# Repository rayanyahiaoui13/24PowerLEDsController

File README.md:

# Well Illumination System

The goal of this system is to provide independent and precise control of a 24-LED matrix composed of high-power LEDs to independently illuminate 24 wells of a Greiner plate containing duckweed. This setup is integrated within a Jubilee robot architecture (a 3D printer transformed into a plant culture robot). The architecture is divided into two main stages: two dedicated PCA9685 PWM controllers that handle 12 channels each, and individual power modules equipped with AL8861 components. 

## 1. 24-LED Control Board

### Power and Regulation Module
This module converts the main 12V input into a stable 3.3V supply to power the ESP32 microcontroller and the PCA9685 PWM drivers.

* **Regulator**: It uses a TSR1-2433E buck switching converter for high energy efficiency. 
* **Protection**: A D1 diode protects the circuit against reverse polarity. 
* **Diagnostics**: A green LED (D2) indicates when the system is powered. 

### Microcontroller (ESP32)
The ESP32 executes the embedded program and transmits brightness instructions via I2C (SDA/SCL). Pull-up resistors (R1, R2) ensure stable data transmission. 

### PWM Drivers (PCA9685)
Two PCA9685PW chips generate 24 stable PWM signals at 400 Hz. 
* **Addressing**: Driver 1 (U3) is at 0x40; Driver 2 (U4) is at 0x41. 
* **Stability**: Decoupling capacitors (C3-C6) are placed close to the VDD pins.

### Constant Current LED Drivers (AL8861)
This power stage translates the PWM signals into constant current for the LEDs.
* **Efficiency**: Uses a Buck switching regulator to minimize heat.
* **Current Setting**: Nominal current is hardware-defined at 300 mA via a 0.33 Ω resistor (R4).

## 2. LED Plate
This secondary PCB houses the 24 high-power OSLON SSL 80 LEDs
* **Thermal Management**: Uses an **aluminum plate** instead of standard FR4 to dissipate intense heat. 
* **Geometry**: LEDs are arranged in a matrix with 19.5 mm spacing to align with the 24-well plate. 
* **Optics**: Convergent lenses are housed in a custom 3D-printed piece to focus light.

## 3. Legacy Box UI (Bonus)
A 3D-printed box housing a legacy interface with a screen and rotary encoder to manually control brightness.

## Documentation & Links
* **General Git**: [science-jubilee](https://github.com/leosabatie-eng/science-jubilee)

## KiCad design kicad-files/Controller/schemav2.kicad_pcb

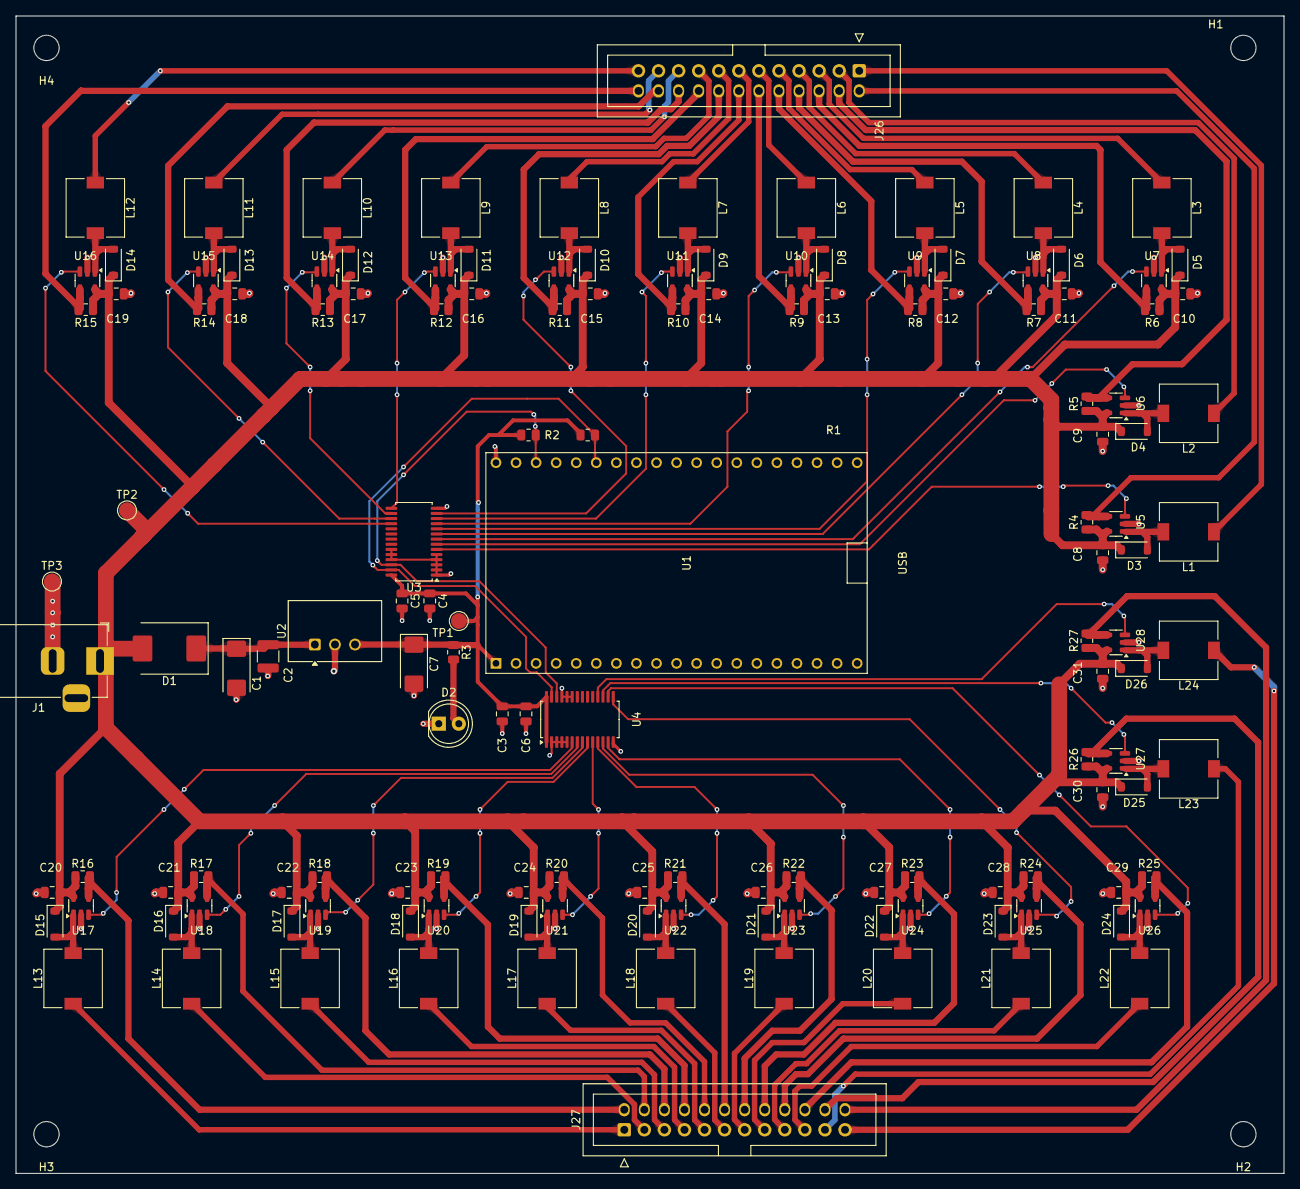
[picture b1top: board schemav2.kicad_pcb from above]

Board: 2 copper layers, 160.5 x 146.5 mm, 146 parts (0 on the bottom side), 103 nets.

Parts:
C1: 10u; CP_EIA-6032-28_Kemet-C
C2: 100n; C_1210_3225Metric
C3, C4, C8, C9, C10, C11, C12, C13, C14, C15, C16, C17, C18, C19, C20, C21, C22, C23, C24, C25, C26, C27, C28, C29, C30, C31: 10uF; C_0805_2012Metric
C5, C6: 0.1uF; C_0805_2012Metric
C7: 100u; CP_EIA-6032-28_Kemet-C
D1: D_Schottky; D_SMC
D2: LED VERTE; LED_D5.0mm
D3, D4, D5, D6, D7, D8, D9, D10, D11, D12, D13, D14, D15, D16, D17, D18, D19, D20, D21, D22, D23, D24, D25, D26: D_Schottky; D_SOD-123
H1, H2, H3, H4: MountingHole; MountingHole_3.2mm_M3
J1: PJ-102AH; BarrelJack_Horizontal
J26, J27: Conn_02x12_Odd_Even; IDC-Header_2x12_P2.54mm_Vertical
L1, L2, L3, L4, L5, L6, L7, L8, L9, L10, L11, L12, L13, L14, L15, L16, L17, L18, L19, L20, L21, L22, L23, L24: 68uH; L_7.3x7.3_H4.5
R1, R2: 4.7k; R_0805_2012Metric
R3: 220; R_0805_2012Metric
R4, R5, R6, R7, R8, R9, R10, R11, R12, R13, R14, R15, R16, R17, R18, R19, R20, R21, R22, R23, R24, R25, R26, R27: 0.33R; R_0805_2012Metric
TP1, TP2, TP3: TestPoint; TestPoint_Pad_D2.0mm
U1: ESP32-DEVKITC
U2: TSR1-2433E; Converter_DCDC_TRACO_TSR1-xxxxE_THT
U3, U4: PCA9685PW; TSSOP-28_4.4x9.7mm_P0.65mm
U5, U6, U7, U8, U9, U10, U11, U12, U13, U14, U15, U16, U17, U18, U19, U20, U21, U22, U23, U24, U25, U26, U27, U28: AL8861Y-13; SOT-23-5

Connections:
+3V3: C3.1, C4.1, C5.1, C6.1, C7.1, R1.1, R2.2, R3.1, TP1.1, U1.1 (3V3), U2.3 (Vout), U3.28 (VDD), U4.1 (A0), U4.28 (VDD)
/LED0+: J26.2, R4.2, U5.4 (ISENSE)
/LED0-: J26.1, L1.1
/LED1+: J26.4, R5.2, U6.4 (ISENSE)
/LED1-: J26.3, L2.1
/LED2+: J26.6, R6.2, U7.4 (ISENSE)
/LED2-: J26.5, L3.1
/LED3+: J26.8, R7.2, U8.4 (ISENSE)
/LED3-: J26.7, L4.1
/LED4+: J26.10, R8.2, U9.4 (ISENSE)
/LED4-: J26.9, L5.1
/LED5+: J26.12, R9.2, U10.4 (ISENSE)
/LED5-: J26.11, L6.1
/LED6+: J26.14, R10.2, U11.4 (ISENSE)
/LED6-: J26.13, L7.1
/LED7+: J26.16, R11.2, U12.4 (ISENSE)
/LED7-: J26.15, L8.1
/LED8+: J26.18, R12.2, U13.4 (ISENSE)
/LED8-: J26.17, L9.1
/LED9+: J26.20, R13.2, U14.4 (ISENSE)
/LED9-: J26.19, L10.1
/LED10+: J26.22, R14.2, U15.4 (ISENSE)
/LED10-: J26.21, L11.1
/LED11+: J26.24, R15.2, U16.4 (ISENSE)
/LED11-: J26.23, L12.1
/LED12+: J27.2, R16.2, U17.4 (ISENSE)
/LED12-: J27.1, L13.1
/LED13+: J27.4, R17.2, U18.4 (ISENSE)
/LED13-: J27.3, L14.1
/LED14+: J27.6, R18.2, U19.4 (ISENSE)
/LED14-: J27.5, L15.1
/LED15+: J27.8, R19.2, U20.4 (ISENSE)
/LED15-: J27.7, L16.1
/LED16+: J27.10, R20.2, U21.4 (ISENSE)
/LED16-: J27.9, L17.1
/LED17+: J27.12, R21.2, U22.4 (ISENSE)
/LED17-: J27.11, L18.1
/LED18+: J27.14, R22.2, U23.4 (ISENSE)
/LED18-: J27.13, L19.1
/LED19+: J27.16, R23.2, U24.4 (ISENSE)
/LED19-: J27.15, L20.1
/LED20+: J27.18, R24.2, U25.4 (ISENSE)
/LED20-: J27.17, L21.1
/LED21+: J27.20, R25.2, U26.4 (ISENSE)
/LED21-: J27.19, L22.1
/LED22+: J27.22, R26.2, U27.4 (ISENSE)
/LED22-: J27.21, L23.1
/LED23+: J27.24, R27.2, U28.4 (ISENSE)
/LED23-: J27.23, L24.1
/PWM 0: U3.6 (LED0), U5.3 (VSET)
/PWM 1: U3.7 (LED1), U6.3 (VSET)
/PWM 2: U3.8 (LED2), U7.3 (VSET)
/PWM 3: U3.9 (LED3), U8.3 (VSET)
/PWM 4: U3.10 (LED4), U9.3 (VSET)
/PWM 5: U3.11 (LED5), U10.3 (VSET)
/PWM 6: U3.12 (LED6), U11.3 (VSET)
/PWM 7: U3.13 (LED7), U12.3 (VSET)
/PWM 8: U3.15 (LED8), U13.3 (VSET)
/PWM 9: U3.16 (LED9), U14.3 (VSET)
/PWM 10: U3.17 (LED10), U15.3 (VSET)
/PWM 11: U3.18 (LED11), U16.3 (VSET)
/PWM 12: U4.6 (LED0), U17.3 (VSET)
/PWM 13: U4.7 (LED1), U18.3 (VSET)
/PWM 14: U4.8 (LED2), U19.3 (VSET)
/PWM 15: U4.9 (LED3), U20.3 (VSET)
/PWM 16: U4.10 (LED4), U21.3 (VSET)
/PWM 17: U4.11 (LED5), U22.3 (VSET)
/PWM 18: U4.12 (LED6), U23.3 (VSET)
/PWM 19: U4.13 (LED7), U24.3 (VSET)
/PWM 20: U4.15 (LED8), U25.3 (VSET)
/PWM 21: U4.16 (LED9), U26.3 (VSET)
/PWM 22: U4.17 (LED10), U27.3 (VSET)
/PWM 23: U4.18 (LED11), U28.3 (VSET)
/SCL: R2.1, U1.36 (IO22), U3.26 (SCL), U4.26 (SCL)
/SDA: R1.2, U1.33 (IO21), U3.27 (SDA), U4.27 (SDA)
GND: C1.2, C2.2, C3.2, C4.2, C5.2, C6.2, C7.2, C8.2, C9.2, C10.2, C11.2, C12.2, C13.2, C14.2, C15.2, C16.2, C17.2, C18.2, C19.2, C20.2, C21.2, C22.2, C23.2, C24.2, C25.2, C26.2, C27.2, C28.2, C29.2, C30.2, C31.2, D2.1 (K), J1.2, TP3.1, U1.38 (GND3), U2.2 (GND), U3.1 (A0), U3.2 (A1), U3.3 (A2), U3.4 (A3), U3.5 (A4), U3.14 (VSS), U3.23 (~OE), U3.24 (A5), U3.25 (EXTCLK), U4.2 (A1), U4.3 (A2), U4.4 (A3), U4.5 (A4), U4.14 (VSS), U4.23 (~OE), U4.24 (A5), U4.25 (EXTCLK), U5.2 (GND), U6.2 (GND), U7.2 (GND), U8.2 (GND), U9.2 (GND), U10.2 (GND), U11.2 (GND), U12.2 (GND), U13.2 (GND), U14.2 (GND), U15.2 (GND), U16.2 (GND), U17.2 (GND), U18.2 (GND), U19.2 (GND), U20.2 (GND), U21.2 (GND), U22.2 (GND), U23.2 (GND), U24.2 (GND), U25.2 (GND), U26.2 (GND), U27.2 (GND), U28.2 (GND)
unnamed: C1.1, C2.1, D1.1 (K), U2.1 (Vin)
unnamed: D2.2 (A), R3.2
unnamed: D3.2 (A), L1.2, U5.1 (LX)
unnamed: D4.2 (A), L2.2, U6.1 (LX)
unnamed: D5.2 (A), L3.2, U7.1 (LX)
unnamed: D6.2 (A), L4.2, U8.1 (LX)
unnamed: D7.2 (A), L5.2, U9.1 (LX)
unnamed: D8.2 (A), L6.2, U10.1 (LX)
unnamed: D9.2 (A), L7.2, U11.1 (LX)
unnamed: D10.2 (A), L8.2, U12.1 (LX)
unnamed: D11.2 (A), L9.2, U13.1 (LX)
unnamed: D12.2 (A), L10.2, U14.1 (LX)
unnamed: D13.2 (A), L11.2, U15.1 (LX)
unnamed: D14.2 (A), L12.2, U16.1 (LX)
unnamed: D15.2 (A), L13.2, U17.1 (LX)
unnamed: D16.2 (A), L14.2, U18.1 (LX)
unnamed: D17.2 (A), L15.2, U19.1 (LX)
unnamed: D18.2 (A), L16.2, U20.1 (LX)
unnamed: D19.2 (A), L17.2, U21.1 (LX)
unnamed: D20.2 (A), L18.2, U22.1 (LX)
unnamed: D21.2 (A), L19.2, U23.1 (LX)
unnamed: D22.2 (A), L20.2, U24.1 (LX)
unnamed: D23.2 (A), L21.2, U25.1 (LX)
unnamed: D24.2 (A), L22.2, U26.1 (LX)
unnamed: D25.2 (A), L23.2, U27.1 (LX)
unnamed: D26.2 (A), L24.2, U28.1 (LX)
VCC: C8.1, C9.1, C10.1, C11.1, C12.1, C13.1, C14.1, C15.1, C16.1, C17.1, C18.1, C19.1, C20.1, C21.1, C22.1, C23.1, C24.1, C25.1, C26.1, C27.1, C28.1, C29.1, C30.1, C31.1, D1.2 (A), D3.1 (K), D4.1 (K), D5.1 (K), D6.1 (K), D7.1 (K), D8.1 (K), D9.1 (K), D10.1 (K), D11.1 (K), D12.1 (K), D13.1 (K), D14.1 (K), D15.1 (K), D16.1 (K), D17.1 (K), D18.1 (K), D19.1 (K), D20.1 (K), D21.1 (K), D22.1 (K), D23.1 (K), D24.1 (K), D25.1 (K), D26.1 (K), J1.1, R4.1, R5.1, R6.1, R7.1, R8.1, R9.1, R10.1, R11.1, R12.1, R13.1, R14.1, R15.1, R16.1, R17.1, R18.1, R19.1, R20.1, R21.1, R22.1, R23.1, R24.1, R25.1, R26.1, R27.1, TP2.1, U5.5 (VIN), U6.5 (VIN), U7.5 (VIN), U8.5 (VIN), U9.5 (VIN), U10.5 (VIN), U11.5 (VIN), U12.5 (VIN), U13.5 (VIN), U14.5 (VIN), U15.5 (VIN), U16.5 (VIN), U17.5 (VIN), U18.5 (VIN), U19.5 (VIN), U20.5 (VIN), U21.5 (VIN), U22.5 (VIN), U23.5 (VIN), U24.5 (VIN), U25.5 (VIN), U26.5 (VIN), U27.5 (VIN), U28.5 (VIN)

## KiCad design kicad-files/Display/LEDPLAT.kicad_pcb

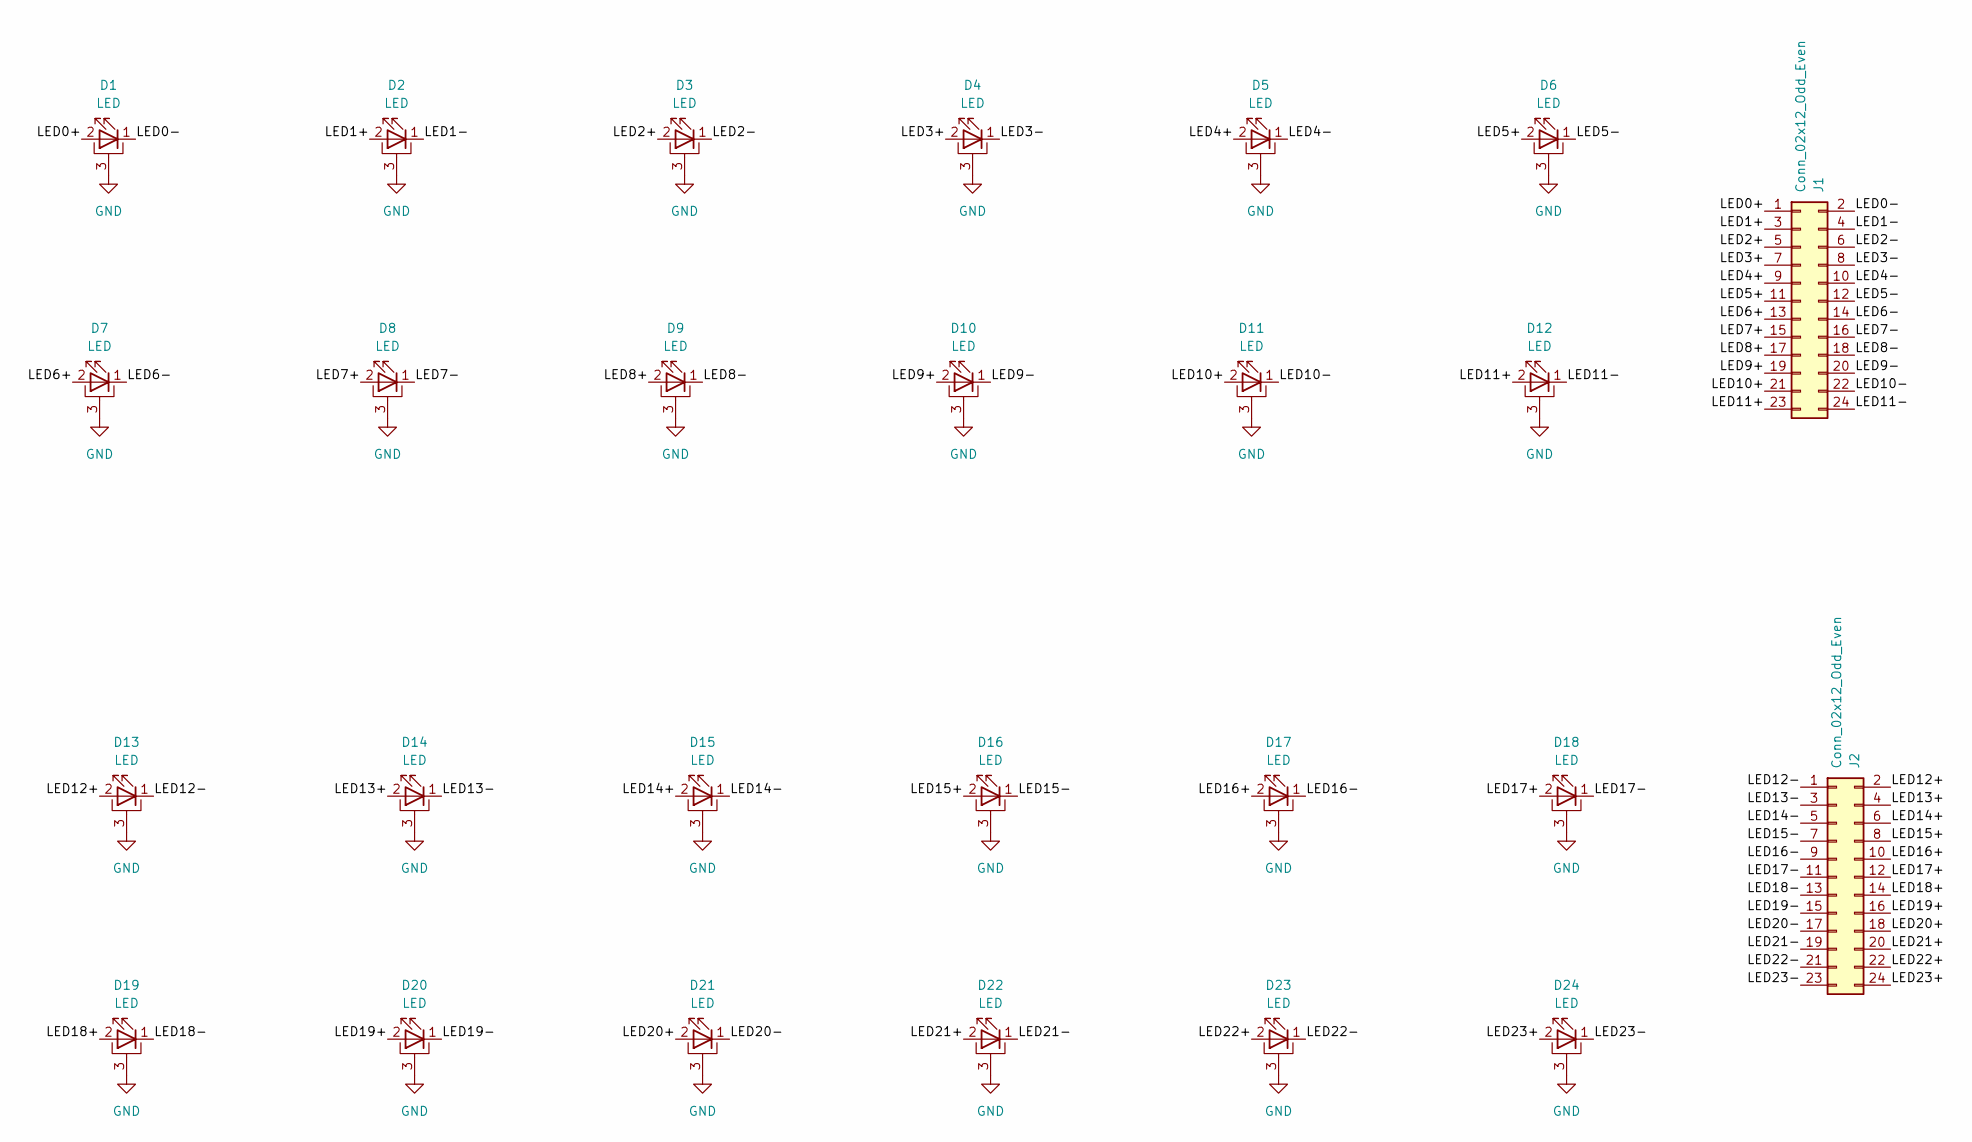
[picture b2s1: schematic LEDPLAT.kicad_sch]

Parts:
D1, D2, D3, D4, D5, D6, D7, D8, D9, D10, D11, D12, D13, D14, D15, D16, D17, D18, D19, D20, D21, D22, D23, D24: LED; LED_OSLON_SSL80
J1, J2: Conn_02x12_Odd_Even; PinHeader_2x12_P2.54mm_Vertical_SMD

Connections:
/LED0+: D1.2 (A), J1.1
/LED0-: D1.1 (K), J1.2
/LED1+: D2.2 (A), J1.3
/LED1-: D2.1 (K), J1.4
/LED2+: D3.2 (A), J1.5
/LED2-: D3.1 (K), J1.6
/LED3+: D4.2 (A), J1.7
/LED3-: D4.1 (K), J1.8
/LED4+: D5.2 (A), J1.9
/LED4-: D5.1 (K), J1.10
/LED5+: D6.2 (A), J1.11
/LED5-: D6.1 (K), J1.12
/LED6+: D7.2 (A), J1.13
/LED6-: D7.1 (K), J1.14
/LED7+: D8.2 (A), J1.15
/LED7-: D8.1 (K), J1.16
/LED8+: D9.2 (A), J1.17
/LED8-: D9.1 (K), J1.18
/LED9+: D10.2 (A), J1.19
/LED9-: D10.1 (K), J1.20
/LED10+: D11.2 (A), J1.21
/LED10-: D11.1 (K), J1.22
/LED11+: D12.2 (A), J1.23
/LED11-: D12.1 (K), J1.24
/LED12+: D13.2 (A), J2.2
/LED12-: D13.1 (K), J2.1
/LED13+: D14.2 (A), J2.4
/LED13-: D14.1 (K), J2.3
/LED14+: D15.2 (A), J2.6
/LED14-: D15.1 (K), J2.5
/LED15+: D16.2 (A), J2.8
/LED15-: D16.1 (K), J2.7
/LED16+: D17.2 (A), J2.10
/LED16-: D17.1 (K), J2.9
/LED17+: D18.2 (A), J2.12
/LED17-: D18.1 (K), J2.11
/LED18+: D19.2 (A), J2.14
/LED18-: D19.1 (K), J2.13
/LED19+: D20.2 (A), J2.16
/LED19-: D20.1 (K), J2.15
/LED20+: D21.2 (A), J2.18
/LED20-: D21.1 (K), J2.17
/LED21+: D22.2 (A), J2.20
/LED21-: D22.1 (K), J2.19
/LED22+: D23.2 (A), J2.22
/LED22-: D23.1 (K), J2.21
/LED23+: D24.2 (A), J2.24
/LED23-: D24.1 (K), J2.23
GND: D1.3 (PAD), D2.3 (PAD), D3.3 (PAD), D4.3 (PAD), D5.3 (PAD), D6.3 (PAD), D7.3 (PAD), D8.3 (PAD), D9.3 (PAD), D10.3 (PAD), D11.3 (PAD), D12.3 (PAD), D13.3 (PAD), D14.3 (PAD), D15.3 (PAD), D16.3 (PAD), D17.3 (PAD), D18.3 (PAD), D19.3 (PAD), D20.3 (PAD), D21.3 (PAD), D22.3 (PAD), D23.3 (PAD), D24.3 (PAD)

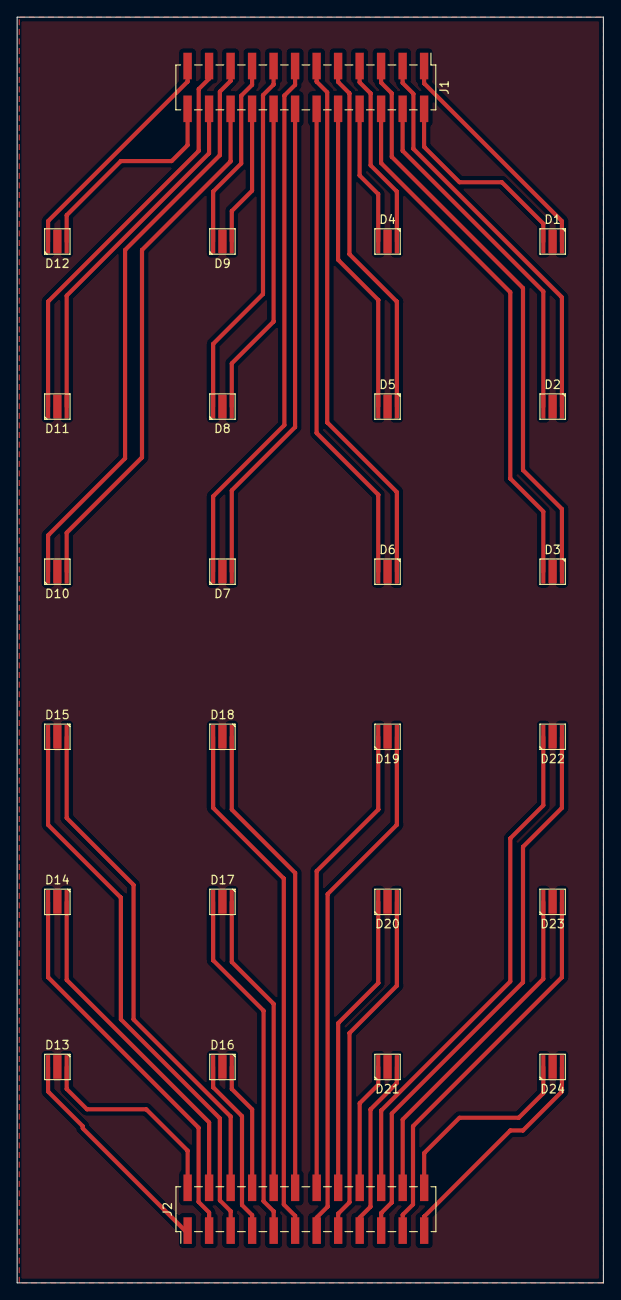
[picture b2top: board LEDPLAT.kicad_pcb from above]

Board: 2 copper layers, 69.2 x 149.5 mm, 26 parts (0 on the bottom side), 49 nets.

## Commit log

2026-04-29 Create p
2026-04-29 Create t
2026-04-29 Create r
2026-05-05 Add README for Well Illumination System
    Added detailed documentation for the Well Illumination System, including descriptions of the control board, power modules, and LED plate.
2026-05-05 Update README with detailed system description
    Expanded the description of the system to include its application in illuminating wells of a Greiner plate and its integration with a Jubilee robot architecture.
2026-05-07 Add controller PCB image to README
    Added an image of the controller PCB to the README.
2026-05-07 Fix image path in README.md
2026-05-07 Change image in README from display to controller PCB
    Updated image references in the README for clarity.
